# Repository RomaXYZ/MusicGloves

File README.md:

# EE445L_Final_Project
Codebase for EE445L final project, Spring 2022 (music gloves lol)

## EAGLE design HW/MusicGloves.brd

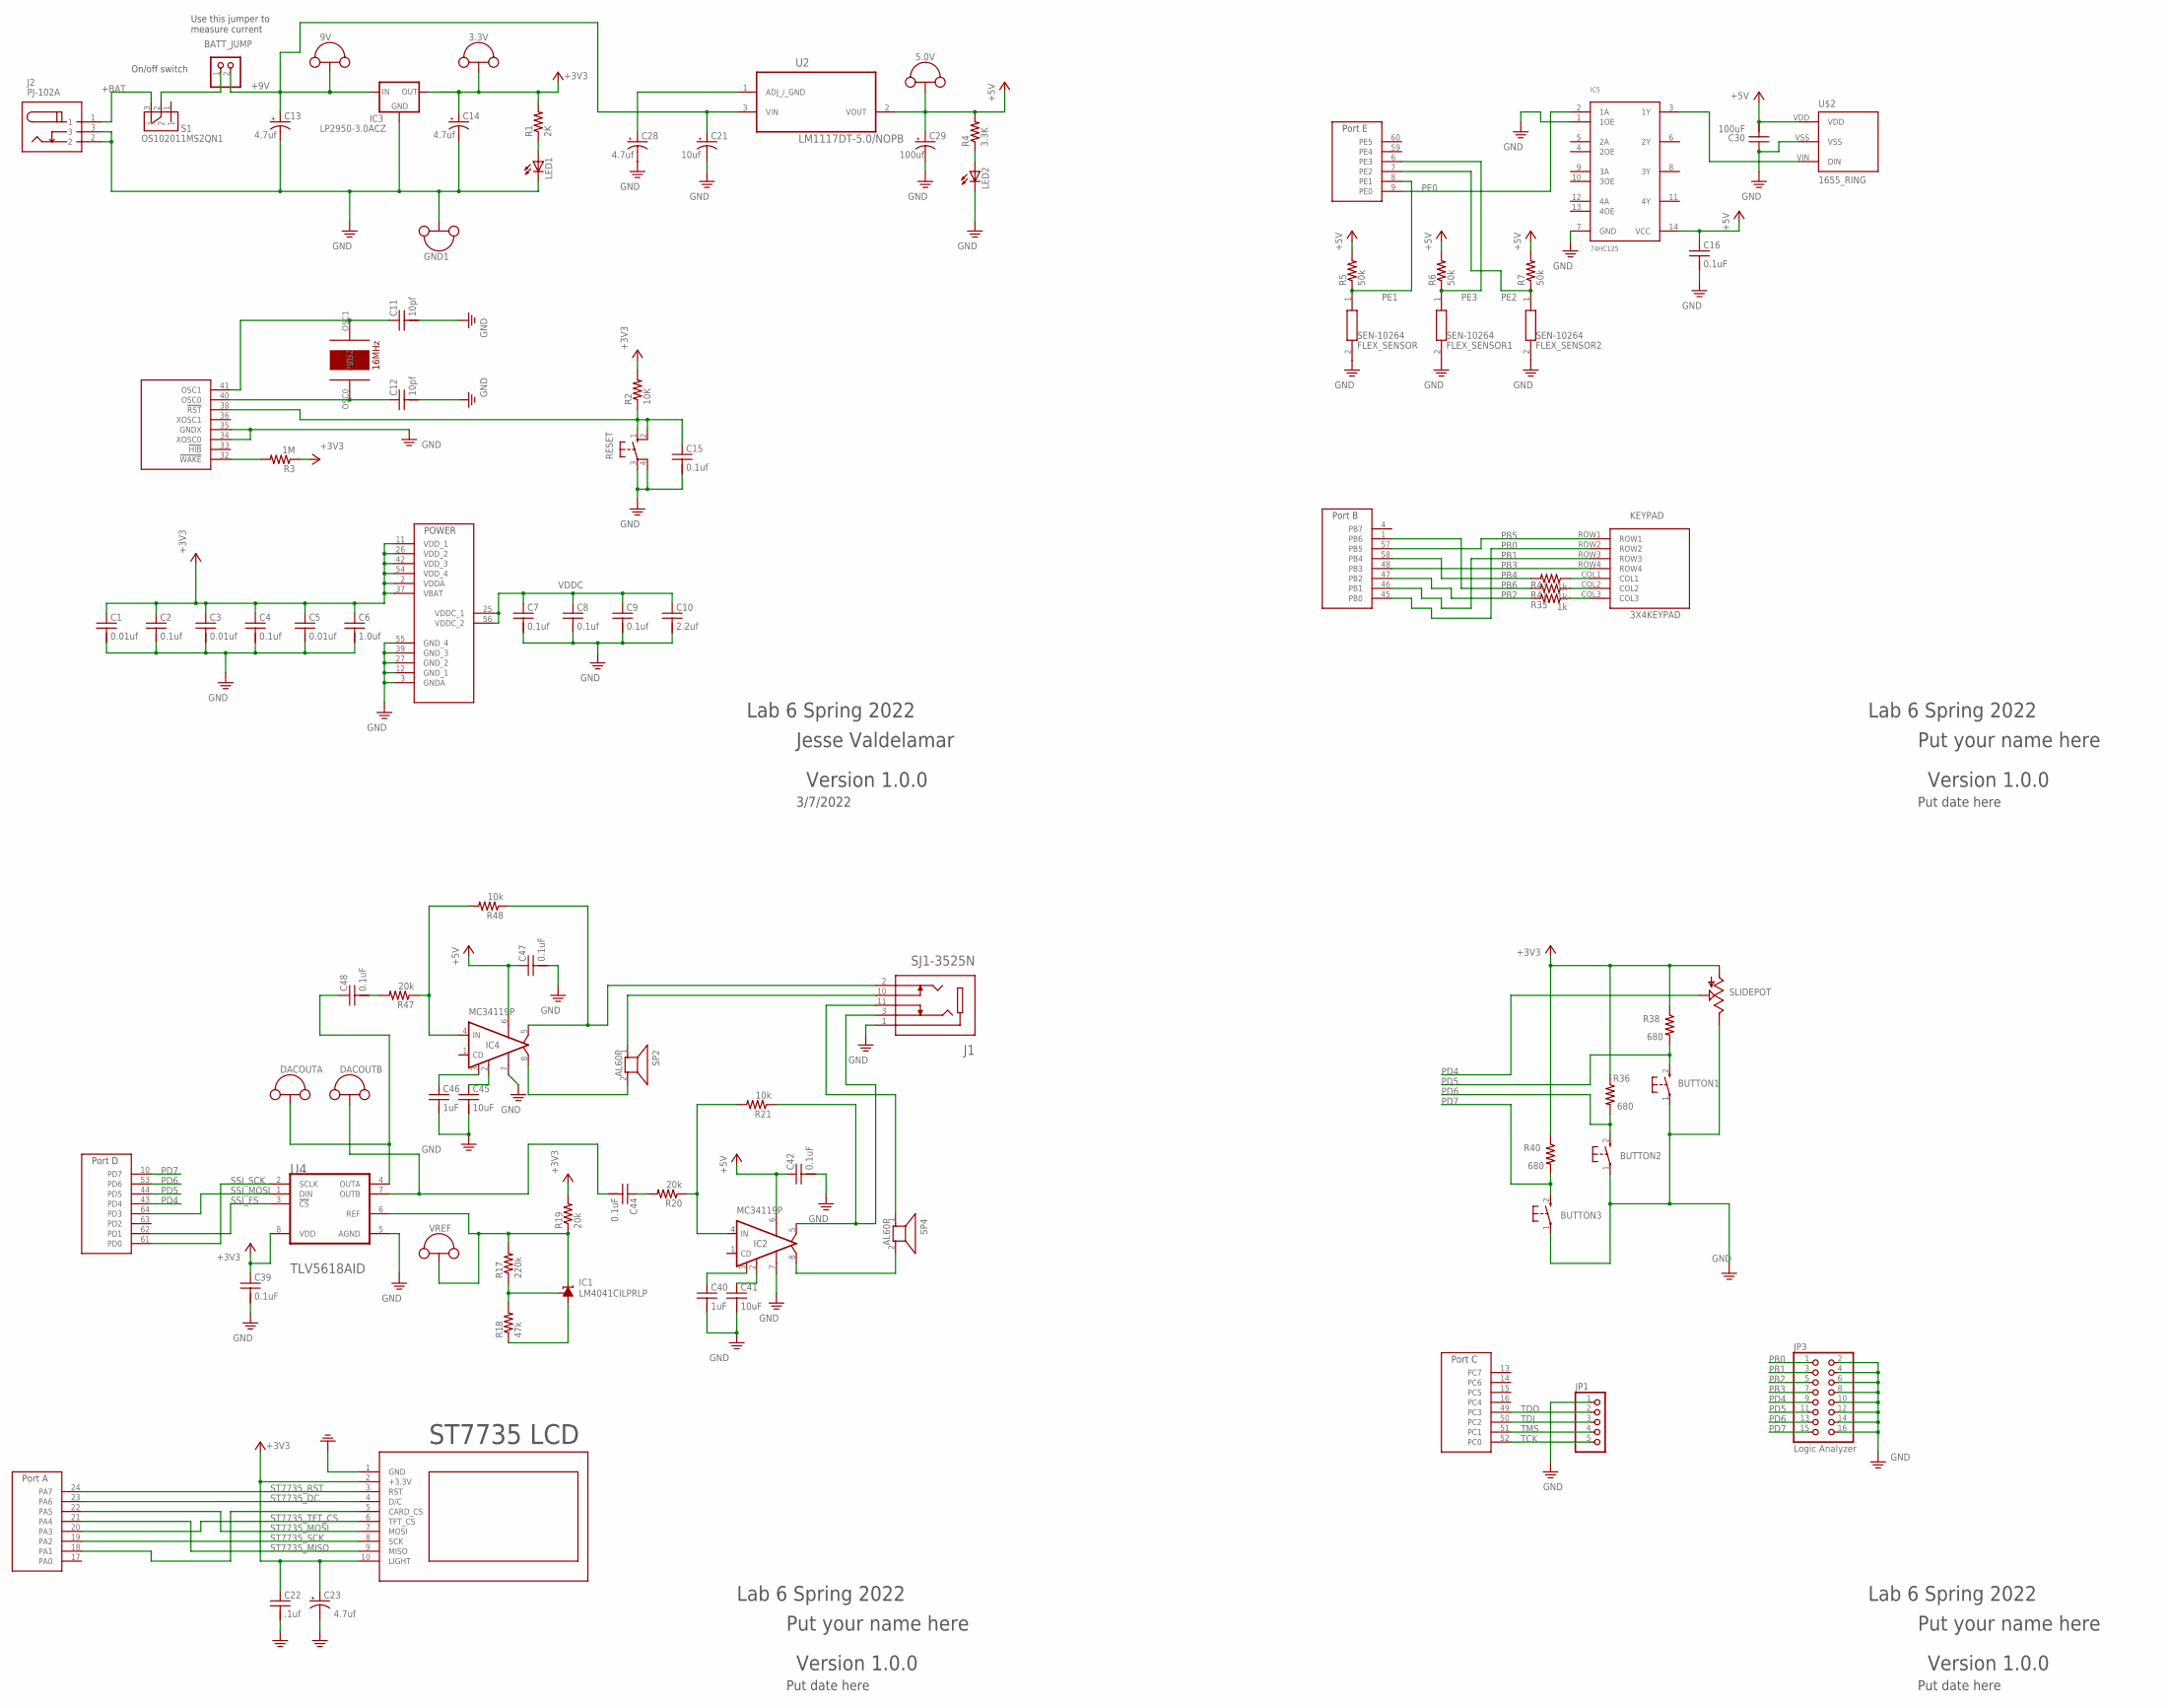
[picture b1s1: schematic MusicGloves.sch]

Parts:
3.3V, 5.0V, 9V: TP_LOOP
BATT_JUMP: PINHD-1X2; 1X02
BUTTON1, BUTTON2, BUTTON3: B3F_1052_2HOLE; B3F-10XX_2HOLE
C1, C3, C5: 0.01uf; CAP100MIL
C2, C4, C7, C8, C9, C15: 0.1uf; CAP100MIL
C6: 1.0uf; CAP100MIL
C10: 2.2uf; CAP100MIL
C11, C12: 10pf; CAP100MIL
C13, C14, C23, C28: 4.7uf; CAP200MILPOLARIZED
C16, C39, C42, C44, C47, C48: 0.1uF; CAP200MIL
C21: 10uf; CAP200MILPOLARIZED
C22: .1uf; CAP200MIL
C29: 100uf; CAP200MILPOLARIZED
C30: 100uF; CAP200MIL
C40, C46: 1uF; CAP200MIL
C41, C45: 10uF; CAP200MIL
DACOUTA: TP_LOOP
DACOUTB: TP_LOOP
FLEX_SENSOR, FLEX_SENSOR1, FLEX_SENSOR2: SEN-10264; RESAD2700W1900L700D500
GND1: TP_LOOP
IC1: LM4041CILPRLP; LP_O-PBCY-W3
IC2, IC4: MC34119P; DIL08
IC3: LP2950-3.0ACZ; TO92
IC5: 74HC125; SOIC-14
J1: SJ1-3525N; CUI_SJ1-3525N
J2: PJ-102A; PJ-102AH
JP1: PINHD-1X5; 1X05
JP3: Logic Analyzer; 2X08
KEYPAD: 3X4KEYPAD
LED1, LED2: LED3MM
R1: 2K; RES200MIL
R2: 10K; RES200MIL
R3: 1M; RES200MIL
R4: 3.3K; RES200MIL
R5, R6, R7: 50k; RES200MIL
R17: 220k; RES200MIL
R18: 47k; RES200MIL
R19, R20, R47: 20k; RES200MIL
R21, R48: 10k; RES200MIL
R35, R41, R43: 1k; 0204/5
R36, R38, R40: 680; 0204/5
RESET: B3F-1052; B3F-10XX
S1: OS102011MS2QN1; SW_OS102011MS2QN1
SLIDEPOT: POTENTIOMETER_PTA2043B25U; PTA2043
SP2, SP4: AL60P
U1: TM4C123GH6PM; QFP50P1200X1200X160-64N
U2: LM1117DT-5.0/NOPB; TO228P970X238-3N
U4: TEXAS_INSTRUMENTS_TLV5618AIDTEXAS_INSTRUMENTS_TLV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; TEXAS_INSTRUMENTS_TLV5618AID_0
U$2: 1655_RING; LED_1655_RING
U$3: ST7735
VREF: TP_LOOP
Y1: 16MHZ_CRYSTAL

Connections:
+3V1: IC1.2 (C), R17.2, R19.1, U4.6 (REF), VREF.P$1, VREF.P$2
+3V2: C48.1, DACOUTA.P$1, DACOUTA.P$2, U4.4 (OUTA)
+3V3: 3.3V.P$1, 3.3V.P$2, C1.1, C2.1, C3.1, C4.1, C5.1, C6.1, C14.+, C22.1, C23.+, C39.1, IC3.1 (OUT), R1.2, R2.2, R3.1, R19.2, R36.1, R38.1, R40.1, SLIDEPOT.3 (A), U1.2 (VDDA), U1.11 (VDD_1), U1.26 (VDD_2), U1.37 (VBAT), U1.42 (VDD_3), U1.54 (VDD_4), U4.8 (VDD), U$3.2 (+3.3V), U$3.10 (LIGHT)
+3V4: C44.2, DACOUTB.P$1, DACOUTB.P$2, U4.7 (OUTB)
+5V: 5.0V.P$1, 5.0V.P$2, C16.1, C29.+, C30.2, C42.1, C47.1, IC2.6 (VCC), IC4.6 (VCC), IC5.14 (VCC), R4.2, R5.2, R6.2, R7.2, U2.2 (VOUT), U$2.VDD
+9V: 9V.P$1, 9V.P$2, BATT_JUMP.2, C13.+, C21.+, IC3.3 (IN), U2.3 (VIN)
+BAT: J2.1, S1.3
COL1: KEYPAD.COL1, R43.1
COL2: KEYPAD.COL2, R41.1
COL3: KEYPAD.COL3, R35.1
GND: BUTTON1.1, BUTTON2.1, BUTTON3.1, C1.2, C2.2, C3.2, C4.2, C5.2, C6.2, C7.2, C8.2, C9.2, C10.2, C11.2, C12.2, C13.-, C14.-, C15.2, C16.2, C21.-, C22.2, C23.-, C28.-, C29.-, C30.1, C39.2, C40.2, C41.2, C42.2, C45.2, C46.2, C47.2, FLEX_SENSOR.2, FLEX_SENSOR1.2, FLEX_SENSOR2.2, GND1.P$1, GND1.P$2, IC2.7 (GND), IC3.2 (GND), IC4.7 (GND), IC5.1 (1OE), IC5.7 (GND), J1.1, J2.2, J2.3, JP1.1, JP3.2, JP3.4, JP3.6, JP3.8, JP3.10, JP3.12, JP3.14, JP3.16, LED1.K (C), LED2.K (C), RESET.3, RESET.4 (P1), SLIDEPOT.1 (E), U1.3 (GNDA), U1.12 (GND_1), U1.27 (GND_2), U1.34 (XOSC0), U1.35 (GNDX), U1.39 (GND_3), U1.55 (GND_4), U4.5 (AGND), U$2.VSS, U$3.1 (GND)
unnamed: J1.10, SP2.1
unnamed: J1.11, SP4.1
unnamed: C44.1, R20.2
unnamed: C28.+, U2.1 (ADJ_/_GND)
unnamed: IC2.4 (IN), R20.1, R21.2
unnamed: IC2.8 (VO2), SP4.2
unnamed: C41.1, IC2.2 (FC2)
unnamed: C40.1, IC2.3 (FC1)
unnamed: U1.18 (PA1), U$3.5 (CARD_CS)
unnamed: IC5.3 (1Y), U$2.VIN (DIN)
unnamed: C48.2, R47.2
unnamed: IC4.4 (IN), R47.1, R48.2
unnamed: IC4.8 (VO2), SP2.2
unnamed: C45.1, IC4.2 (FC2)
unnamed: C46.1, IC4.3 (FC1)
OSC0: C12.1, U1.40 (OSC0), Y1.OSC0
OSC1: C11.1, U1.41 (OSC1), Y1.OSC1
PB0: JP3.1, KEYPAD.ROW2, U1.45 (PB0)
PB1: JP3.3, KEYPAD.ROW3, U1.46 (PB1)
PB2: JP3.5, R35.2, U1.47 (PB2)
PB3: JP3.7, KEYPAD.ROW4, U1.48 (PB3)
PB4: R43.2, U1.58 (PB4)
PB5: KEYPAD.ROW1, U1.57 (PB5)
PB6: R41.2, U1.1 (PB6)
PD4: JP3.9, SLIDEPOT.2 (S), U1.43 (PD4)
PD5: BUTTON1.2 (S), JP3.11, R38.2, U1.44 (PD5)
PD6: BUTTON2.2 (S), JP3.13, R36.2, U1.53 (PD6)
PD7: BUTTON3.2 (S), JP3.15, R40.2, U1.10 (PD7)
PE0: IC5.2 (1A), U1.9 (PE0)
PE1: FLEX_SENSOR.1, R5.1, U1.8 (PE1)
PE2: FLEX_SENSOR2.1, R7.1, U1.7 (PE2)
PE3: FLEX_SENSOR1.1, R6.1, U1.6 (PE3)
POWERLED: LED1.A, R1.1
POWERLED1: LED2.A, R4.1
POWERLED3: IC4.5 (VO1), J1.2, R48.1
POWERLED14: IC1.1 (FB), R17.1, R18.2
POWERLED15: IC1.3 (A), R18.1
POWERLED17: IC2.5 (VO1), J1.3, R21.1
RESET: C15.1, R2.1, RESET.1 (S), RESET.2 (S1), U1.38 (!RST)
SSI_FS: U1.62 (PD1), U4.3 (!CS!)
SSI_MOSI: U1.64 (PD3), U4.1 (DIN)
SSI_SCK: U1.61 (PD0), U4.2 (SCLK)
ST7735_DC: U1.23 (PA6), U$3.4 (D/C)
ST7735_MISO: U1.21 (PA4), U$3.9 (MISO)
ST7735_MOSI: U1.22 (PA5), U$3.7 (MOSI)
ST7735_RST: U1.24 (PA7), U$3.3 (RST)
ST7735_SCK: U1.19 (PA2), U$3.8 (SCK)
ST7735_TFT_CS: U1.20 (PA3), U$3.6 (TFT_CS)
SWITCHEDPOWER: BATT_JUMP.1, S1.2
TCK: JP1.5, U1.52 (PC0)
TDI: JP1.3, U1.50 (PC2)
TDO: JP1.2, U1.49 (PC3)
TMS: JP1.4, U1.51 (PC1)
VDDC: C7.1, C8.1, C9.1, C10.1, U1.25 (VDDC_1), U1.56 (VDDC_2)
WAKE: R3.2, U1.32 (!WAKE)

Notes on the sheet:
Use this jumper to measure current
Lab 6 Spring 2022
Jesse Valdelamar
Version 1.0.0
3/7/2022
Put your name here
Put date here
On/off switch
ST7735 LCD

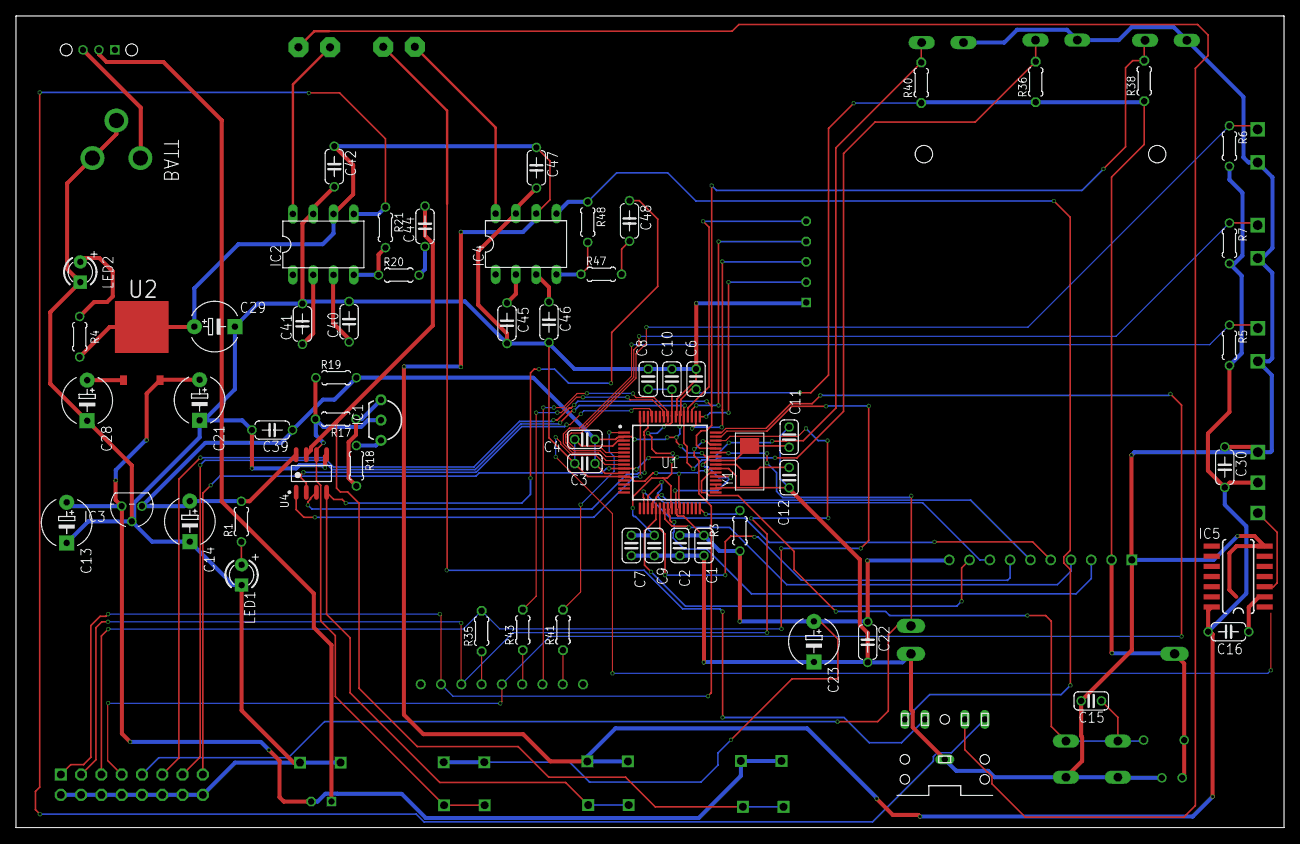
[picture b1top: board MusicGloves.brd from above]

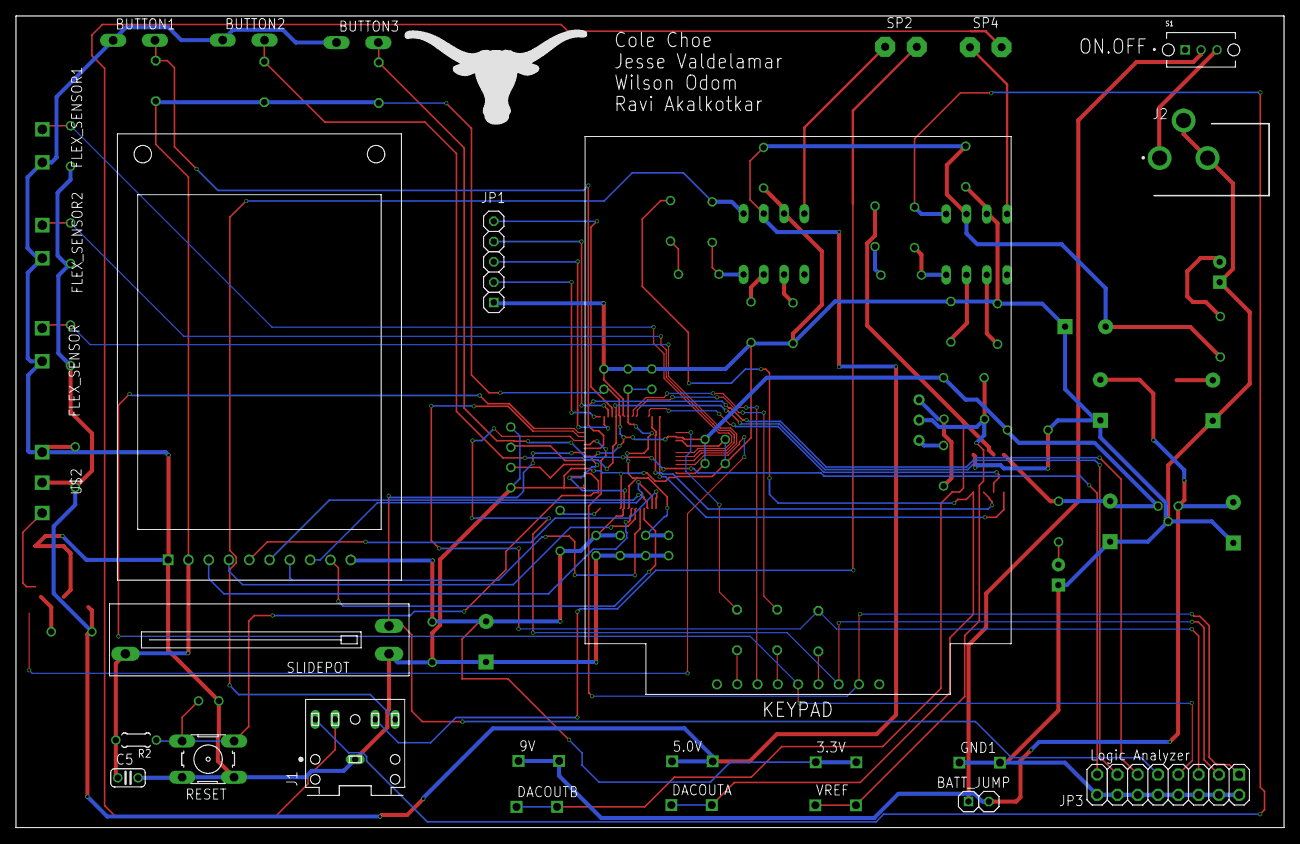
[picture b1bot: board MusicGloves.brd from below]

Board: 2 copper layers, 158.7 x 101.6 mm, 88 parts (26 on the bottom side), 66 nets.

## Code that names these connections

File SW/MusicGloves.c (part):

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 * @note Potential Pinouts:
 *    Backlight (pin 10) connected to +3.3 V
 *    MISO (pin 9) unconnected
 *    SCK (pin 8) connected to PA2 (SSI0Clk)
 *    MOSI (pin 7) connected to PA5 (SSI0Tx)
 *    TFT_CS (pin 6) connected to PA3 (SSI0Fss)
 *    CARD_CS (pin 5) unconnected
 *    Data/Command (pin 4) connected to PA6 (GPIO)
 *    RESET (pin 3) connected to PA7 (GPIO)
 *    VCC (pin 2) connected to +3.3 V
 *    Gnd (pin 1) connected to ground
 * 
 *    Center of 10k-ohm potentiometer connected to PE2/AIN1
 *    Bottom of 10k-ohm potentiometer connected to ground
 *    Top of 10k-ohm potentiometer connected to +3.3V 
 *
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int main_NeoPixel(void) { // Main for testing the neopixels
    DisableInterrupts();
    /* TExaS Debug modes:
       SCOPE,           // PD3
       LOGICANALYZER,   // ???
       SCOPE_PD2,       // PD2
       SCOPE_PE2,       // PE3
       SCOPE_PB5        // PB5
     */
		// Beginning on Initializations
		PLL_Init(Bus80MHz);              // now running at 80 MHz
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int main_lcddisplay(void) { // Main for testing LCD Display
    DisableInterrupts();
    /* TExaS Debug modes:
       SCOPE,           // PD3
       LOGICANALYZER,   // ???
       SCOPE_PD2,       // PD2
       SCOPE_PE2,       // PE3
       SCOPE_PB5        // PB5
     */
		// Beginning on Initializations
		PLL_Init(Bus80MHz);              // now running at 80 MHz
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
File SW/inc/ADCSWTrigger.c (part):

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  ADC0_ACTSS_R |= 0x0008;         // 14) enable sample sequencer 3
}

// PD0 is AIN7
void ADC0_InitSWTriggerSeq3_Ch7(void){ 
  SYSCTL_RCGCADC_R |= 0x0001;   // 7) activate ADC0 
                                  // 1) activate clock for Port D
  SYSCTL_RCGCGPIO_R |= 0x08;  // D
  while((SYSCTL_PRGPIO_R&0x08) != 0x08){};
  GPIO_PORTD_DIR_R &= ~0x01;      // 2) make PE4 input
  GPIO_PORTD_AFSEL_R |= 0x01;     // 3) enable alternate function on PD0
  GPIO_PORTD_DEN_R &= ~0x01;      // 4) disable digital I/O on PD0
  GPIO_PORTD_AMSEL_R |= 0x01;     // 5) enable analog functionality on PD0
    
  while((SYSCTL_PRADC_R&0x0001) != 0x0001){};    // good code, but not yet implemented in simulator

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  delay = SYSCTL_RCGCGPIO_R;
  delay = SYSCTL_RCGCGPIO_R;
  switch(channelNum){
    case 0:                       //      Ain0 is on PE3
      GPIO_PORTE_DIR_R &= ~0x08;  // 3.0) make PE3 input
      GPIO_PORTE_AFSEL_R |= 0x08; // 4.0) enable alternate function on PE3
      GPIO_PORTE_DEN_R &= ~0x08;  // 5.0) disable digital I/O on PE3
      GPIO_PORTE_AMSEL_R |= 0x08; // 6.0) enable analog functionality on PE3
      break;
    case 1:                       //      Ain1 is on PE2
      GPIO_PORTE_DIR_R &= ~0x04;  // 3.1) make PE2 input
      GPIO_PORTE_AFSEL_R |= 0x04; // 4.1) enable alternate function on PE2
      GPIO_PORTE_DEN_R &= ~0x04;  // 5.1) disable digital I/O on PE2
      GPIO_PORTE_AMSEL_R |= 0x04; // 6.1) enable analog functionality on PE2
      break;
    case 2:                       //      Ain2 is on PE1
      GPIO_PORTE_DIR_R &= ~0x02;  // 3.2) make PE1 input
      GPIO_PORTE_AFSEL_R |= 0x02; // 4.2) enable alternate function on PE1
      GPIO_PORTE_DEN_R &= ~0x02;  // 5.2) disable digital I/O on PE1
      GPIO_PORTE_AMSEL_R |= 0x02; // 6.2) enable analog functionality on PE1
      break;
    case 3:                       //      Ain3 is on PE0
      GPIO_PORTE_DIR_R &= ~0x01;  // 3.3) make PE0 input
      GPIO_PORTE_AFSEL_R |= 0x01; // 4.3) enable alternate function on PE0
      GPIO_PORTE_DEN_R &= ~0x01;  // 5.3) disable digital I/O on PE0
      GPIO_PORTE_AMSEL_R |= 0x01; // 6.3) enable analog functionality on PE0
      break;
    case 4:                       //      Ain4 is on PD3
      GPIO_PORTD_DIR_R &= ~0x08;  // 3.4) make PD3 input
      GPIO_PORTD_AFSEL_R |= 0x08; // 4.4) enable alternate function on PD3
      GPIO_PORTD_DEN_R &= ~0x08;  // 5.4) disable digital I/O on PD3
      GPIO_PORTD_AMSEL_R |= 0x08; // 6.4) enable analog functionality on PD3
      break;
    case 5:                       //      Ain5 is on PD2
      GPIO_PORTD_DIR_R &= ~0x04;  // 3.5) make PD2 input
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      GPIO_PORTD_DEN_R &= ~0x04;  // 5.5) disable digital I/O on PD2
      GPIO_PORTD_AMSEL_R |= 0x04; // 6.5) enable analog functionality on PD2
      break;
    case 6:                       //      Ain6 is on PD1
      GPIO_PORTD_DIR_R &= ~0x02;  // 3.6) make PD1 input
      GPIO_PORTD_AFSEL_R |= 0x02; // 4.6) enable alternate function on PD1
      GPIO_PORTD_DEN_R &= ~0x02;  // 5.6) disable digital I/O on PD1
      GPIO_PORTD_AMSEL_R |= 0x02; // 6.6) enable analog functionality on PD1
      break;
    case 7:                       //      Ain7 is on PD0
      GPIO_PORTD_DIR_R &= ~0x01;  // 3.7) make PD0 input
      GPIO_PORTD_AFSEL_R |= 0x01; // 4.7) enable alternate function on PD0
      GPIO_PORTD_DEN_R &= ~0x01;  // 5.7) disable digital I/O on PD0
      GPIO_PORTD_AMSEL_R |= 0x01; // 6.7) enable analog functionality on PD0
      break;
    case 8:                       //      Ain8 is on PE5
      GPIO_PORTE_DIR_R &= ~0x20;  // 3.8) make PE5 input
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      GPIO_PORTE_DEN_R &= ~0x10;  // 5.9) disable digital I/O on PE4
      GPIO_PORTE_AMSEL_R |= 0x10; // 6.9) enable analog functionality on PE4
      break;
    case 10:                      //       Ain10 is on PB4
      GPIO_PORTB_DIR_R &= ~0x10;  // 3.10) make PB4 input
      GPIO_PORTB_AFSEL_R |= 0x10; // 4.10) enable alternate function on PB4
      GPIO_PORTB_DEN_R &= ~0x10;  // 5.10) disable digital I/O on PB4
      GPIO_PORTB_AMSEL_R |= 0x10; // 6.10) enable analog functionality on PB4
      break;
    case 11:                      //       Ain11 is on PB5
      GPIO_PORTB_DIR_R &= ~0x20;  // 3.11) make PB5 input
      GPIO_PORTB_AFSEL_R |= 0x20; // 4.11) enable alternate function on PB5
      GPIO_PORTB_DEN_R &= ~0x20;  // 5.11) disable digital I/O on PB5
      GPIO_PORTB_AMSEL_R |= 0x20; // 6.11) enable analog functionality on PB5
      break;
  }
  SYSCTL_RCGCADC_R |= 0x00000001; // 7) activate ADC0 (actually doesn't work)
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// Sequencer 2 priority: 3rd
// Sequencer 3 priority: 4th (lowest)
// SS2 triggering event: software trigger, busy-wait sampling
// SS2 1st sample source: AIN6 (PD1)
// SS2 2nd sample source: AIN5 (PD2)
// SS2 3st sample source: AIN4 (PD3)
// SS2 interrupts: enabled after 3rd sample but not promoted to controller
// 'task' is a pointer to a user function called in SS2 interrupt
// the user function has three parameters that get the x-, y-, and
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  SYSCTL_RCGCGPIO_R |= 0x08;    // activate clock for Port D
                                // allow time for clock to stabilize
  while((SYSCTL_PRGPIO_R&0x08) == 0){};
  GPIO_PORTD_DIR_R &= ~0x0E;    // make PD3-1 input
  GPIO_PORTD_AFSEL_R |= 0x0E;   // enable alternate function on PD3-1
  GPIO_PORTD_DEN_R &= ~0x0E;    // disable digital I/O on PD3-1
  GPIO_PORTD_AMSEL_R |= 0x0E;   // enable analog functionality on PD3-1
  // **** ADC0 SS2 initialization ****
  SYSCTL_RCGCADC_R |= 0x01;     // activate clock for ADC0
                                // allow time for clock to stabilize
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  uint32_t x, y, z;
  ADC0_PSSI_R = 0x0004;         // 1) initiate SS2
  while((ADC0_RIS_R&0x04)==0){};// 2) wait for conversion done
  x = ADC0_SSFIFO2_R&0xFFF;     // 3A) read 12-bit result from AIN6 (PD1)
  y = ADC0_SSFIFO2_R&0xFFF;     // 3B) read 12-bit result from AIN5 (PD2)
  z = ADC0_SSFIFO2_R&0xFFF;     // 3C) read 12-bit result from AIN4 (PD3)
  UserTask2(x, y, z);           // 4)  call the user function
  ADC0_ISC_R = 0x0004;          // 5) acknowledge completion
}
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}


// Initializes ADC0(PE3), ADC1(PE2), ADC2(PE1) and ADC3(PE0) sampling
// 125k max sampling
// SS2 triggering event: software trigger, busy-wait sampling
// SS2 1st sample source: Ain0 (PE3)
// SS2 2nd sample source: Ain1 (PE2)
// SS2 3rd sample source: Ain2 (PE1)
// SS2 4th sample source: Ain3 (PE0)
// SS2 interrupts: enabled after 4th sample but not promoted to controller
void ADC_Init3210(void){ 
  volatile uint32_t delay;                         
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  SYSCTL_RCGCGPIO_R |= 0x10;      // 1) activate clock for Port E
  while((SYSCTL_PRGPIO_R&0x10) == 0){};
  while((SYSCTL_PRADC_R&0x0001) != 0x0001){};    // good code, but not yet implemented in simulator
  GPIO_PORTE_DIR_R &= ~0x0E;      // 3) make PE3-1 input
  GPIO_PORTE_AFSEL_R |= 0x0E;     // 4) enable alternate function on PE3-1
  GPIO_PORTE_DEN_R &= ~0x0E;      // 5) disable digital I/O on PE3-1
  GPIO_PORTE_PCTL_R = GPIO_PORTE_PCTL_R&0xFFFF000F;
  GPIO_PORTE_AMSEL_R |= 0x0E;     // 6) enable analog functionality on PE3-1
  ADC0_PC_R &= ~0xF;              // 8) clear max sample rate field
  ADC0_PC_R |= 0x1;               //    configure for 125K samples/sec
  ADC0_SSPRI_R = 0x3210;          // 9) Sequencer 3 is lowest priority
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// Busy-wait Analog to digital conversion
// Input: none
// Output: four 12-bit result of ADC conversions
// Samples ADC0(PE3), ADC1(PE2), ADC2(PE1) and ADC3(PE0) 
// 125k max sampling
// software trigger, busy-wait sampling
// data returned by reference
// data[0] is ADC3 (PE0) 0 to 4095
// data[1] is ADC2 (PE1) 0 to 4095
// data[2] is ADC1 (PE2) 0 to 4095
// data[3] is ADC0 (PE3) 0 to 4095
void ADC_In3210(uint32_t data[3]){ 
  ADC0_PSSI_R = 0x0004;            // 1) initiate SS2
  while((ADC0_RIS_R&0x04)==0){};   // 2) wait for conversion done
  //data[0] = ADC0_SSFIFO2_R&0xFFF;  // 3A) PE0 result
  data[0] = ADC0_SSFIFO2_R&0xFFF;  // 3A) PE1 result
  data[1] = ADC0_SSFIFO2_R&0xFFF;  // 3A) PE2 result
  data[2] = ADC0_SSFIFO2_R&0xFFF;  // 3B) PE3 result
  ADC0_ISC_R = 0x0004;             // 4) acknowledge completion
}

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
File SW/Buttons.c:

// filename ******** Buttons.c **************
// This files involves interfacing the buttons and the keypad
// Date: 3/30/2022
// Created by Wilson Odom
// Lab Number 17525
// TA Mohit
// Date of Last Revision: 4/8/2022

/** File includes. */
#include <stdio.h>
#include <stdint.h>
#include "./inc/tm4c123gh6pm.h"
#include "./inc/Timer2A.h"
#include "./inc/Timer3A.h"
#include "./inc/Timer4A.h"
#include "./inc/CortexM.h"

#define NVIC_EN0_INT2           0x00000004  // Interrupt 2 enable
#define NVIC_EN0_INT3           0x00000008  // Interrupt 3 enable

// SW1 corresponds to PC4
// SW2 corresponds to PC5
// SW3 corresponds to PC6
volatile uint8_t SW1, SW2, SW3;
uint16_t switch_debouncing;
uint8_t set = 0;

void switch_debouncer(void);

///****************Button_Init****************
// Initializes 3 Buttons on Ports PC4-PC6
// Remember to change this to match the diagram post-PCB
void Button_Init(void){
	
// Port C version, PC4-PC6
	SYSCTL_RCGCGPIO_R |= 0x04; // Activate clock for Port C
	SW1, SW2, SW3 = 0; // Clear all 3 semaphores
	
	GPIO_PORTC_DIR_R &= ~0x70; // Make PC4-PC6 in
	GPIO_PORTC_DEN_R |= 0x70; // Enable Digital I/o on PC4-PC6
	GPIO_PORTC_IS_R &= ~0x70; // PC4-PC6 is edge sensitive
	GPIO_PORTC_IBE_R &= ~0x70; // PC4-PC6, single edge
	GPIO_PORTC_IEV_R |= 0x70; // Rising edge
	GPIO_PORTC_ICR_R = 0x70; // Clear Flag 4, 5 and 6
	GPIO_PORTC_IM_R |= 0x70; // ARM interrupts
	
	NVIC_PRI0_R = (NVIC_PRI0_R& 0xFF00FFFF) | 0x00400000; // PortC = priority 2
	NVIC_EN0_R = (NVIC_EN0_INT2); // Enable Interrupt 2
	
	switch_debouncing = 0;
	set = 0;
	
	//EnableInterrupts();
	
// Port D Version, PD5-PD7
//	SYSCTL_RCGCGPIO_R |= 0x08; // Activate clock for Port D
//	SW1, SW2, SW3 = 0; // Clear all 3 semaphores
//	
//	GPIO_PORTD_DIR_R &= ~0xD0; // Make PD5-PD7 in
//	GPIO_PORTD_DEN_R |= 0xD0; // Enable Digital I/o on PD5-PD7
//	GPIO_PORTD_IS_R &= ~0xD0; // PD5-PD7 is edge sensitive
//	GPIO_PORTD_IBE_R &= ~0xD0; // PD5-PD7, single edge
//	GPIO_PORTD_IEV_R |= 0xD0; // Rising edge
//	GPIO_PORTD_ICR_R = 0xD0; // Clear Flags for PD5-PD7
//	GPIO_PORTD_IM_R |= 0xD0; // ARM interrupts
//	
//	NVIC_PRI0_R = (NVIC_PRI0_R& 0x0FFFFFFF) | 0x40000000; // PortD = priority 2
//	NVIC_EN0_R = (NVIC_EN0_INT3); // Enable Interrupt 3
//	EnableInterrupts();
		
	
	
}

void GPIOPortC_Handler(void){
	// Debounce, wait 20 ms to find the true value
	if(switch_debouncing == 0){
		
		// Get the value of the of the switches pressed
		if((GPIO_PORTC_RIS_R >> 4) & 0x01){
			SW1 = 1;
			switch_debouncing = 1;
		}else if((GPIO_PORTC_RIS_R >> 5) & 0x01){
			SW2 = 1;
			switch_debouncing = 2;
		}else if((GPIO_PORTC_RIS_R >> 6) & 0x01){
			SW3 = 1;
			switch_debouncing = 3;
		}
		set = 1;
		Timer4A_Init(&switch_debouncer, 1000000, 2);
	}
	GPIO_PORTC_ICR_R = 0x70; // Acknowledge all 3 flags
	
}

//void GPIOPortD_Handler(void){
//		// Debounce, wait 20 ms to find the true value
//	GPIO_PORTD_ICR_R = 0x70; // Acknowledge all 3 flags
//	if(switch_debouncing == 0){
//		SW1 = (GPIO_PORTC_RIS_R & 0x01);
//		SW2 = (GPIO_PORTC_RIS_R >> 1) & 0x01;
//		SW3 = (GPIO_PORTC_RIS_R >> 2) & 0x01;
//		Timer4A_Init(&switch_debouncer, 1600000, 2);
//		switch_debouncing = 1; // You are now debouncing!
//	}
//}

void wait_for_fall(void){
	if(!((GPIO_PORTC_DATA_R>>(3+switch_debouncing))&1)){
		Timer4A_Stop();
		Timer4A_Init(&switch_debouncer, 1000000, 2);
		set=0;
	}
}
void switch_debouncer(void){
		//switch_debouncing = 0; // You are no longer debouncing!
		Timer4A_Stop();
		if(set){
			Timer4A_Init(&wait_for_fall, 1000000, 2);
		}
		else{
			switch_debouncing=0;
		}
}



uint8_t GetSW1(void){
	uint8_t copy = SW1;
	SW1 = 0;
	return(copy);
}
uint8_t GetSW2(void){
	uint8_t copy = SW2;
	SW2 = 0;
	return(copy);
}
uint8_t GetSW3(void){
	uint8_t copy = SW3;
	SW3 = 0;
	return(copy);
}



///****************SlidePot_Init****************
// Initializes a single slide pot on Port PD2 to function as an ADC
// Initializes ADC1
void SlidePot_Init(void){
	volatile uint32_t delay;
	SYSCTL_RCGCADC_R |= 0x00000002; // 1) Activate ADC1
	SYSCTL_RCGCGPIO_R |= 0x08; // 1) Activate clock for Port D
	
	while((SYSCTL_PRGPIO_R  & 0x08) == 0){}; // Wait for Port D clock to stabilize
	while((SYSCTL_PRADC_R & 0x0002) != 0x0002){}; // Wait for ADC2 to stabilize
	
	GPIO_PORTD_DIR_R &= ~0x04; // 3) Make PD2 an input
	GPIO_PORTD_AFSEL_R &= 0x04; // 4) Enable alt function on PD2
	GPIO_PORTD_DEN_R &= ~0x04; // 5) Disable digital I/O on PD2
	GPIO_PORTD_PCTL_R &= 0xFFFFF0FF; // PD2
	GPIO_PORTD_AMSEL_R &= 0x04; // 6) Enable Analog Funct. on PD2
		
	ADC1_PC_R &= ~0xF; 							// 8 )Clear Max Sample Field on ADC1	
	ADC1_PC_R |= 0x1; 							// Configure for 125k samples / second
	ADC1_SSPRI_R = 0x3210;          // 9) Sequencer 3 is lowest priority
  ADC1_ACTSS_R &= ~0x0004;        // 10) disable sample sequencer 2
  ADC1_EMUX_R &= ~0x0F00;         // 11) seq2 is software trigger
  ADC1_SAC_R = 0x06;              // 32-point average
  //ADC1_SSMUX2_R = 0x0123;         // 12) set channels for SS2
	ADC1_SSMUX2_R = 0x0005;         // 12) set channels for SS2, Channel 5	
  ADC1_SSCTL2_R = 0x0006;         // 13) no TS0 D0 IE0 END0 TS1 D1, yes IE1 END1
  ADC1_IM_R &= ~0x0004;           // 14) disable SS2 interrupts
  ADC1_ACTSS_R |= 0x0004;         // 15) enable sample sequencer 2	
			
		
}

int slidePot_Get(void){
	ADC1_PSSI_R = 0x0004; // 1) Initiate SS2
	int data;
	while((ADC1_RIS_R & 0x04) == 0){}; // 2) Wait for conversion to be done
	data = ADC1_SSFIFO2_R & 0xFFF;
	ADC1_ISC_R = 0x0004;
		
	return(data);
}

int GetVolume(void){
	int slidepot = slidePot_Get();
	
	// Map this to 0 - 100
	int temp = (slidepot / 40);
	if(temp < 2){
		return(0);
	}
	else if (temp > 100){
		return(100);
	}
	else{
		return(temp - 1);
	}
}

void KeypadScan1(void);
void KeypadScan2(void);
void keypadDebouncer(void);


int RowData = 0x20;
int prevRowData = 0x08;
int RowNum = 0;
int ColNum = 0;
int pressed = 0;
int scanning = 0;
uint8_t set2 = 0;
///****************Keypad_Init***************
// Initializes a keypad on Ports PB0-PB6
void Keypad_Init(void){
	volatile unsigned long delay;

  SYSCTL_RCGCGPIO_R |= 0x00000002;  // 1) activate clock for Port B
  delay = SYSCTL_RCGCGPIO_R;        // allow time for clock to start
                                    // 2) no need to unlock GPIO Port C
  GPIO_PORTB_AMSEL_R = 0;      			// 3) disable analog on PB0-6
  GPIO_PORTB_PCTL_R = 0; 						// 4) PCTL GPIO on PC0-6
  GPIO_PORTB_DIR_R = 0x2B;       	 	// 5) direction PB2,4,6 input, PB0,1,3,5 output
  GPIO_PORTB_AFSEL_R &= ~0x7F;      // 6) PB0-6 regular port function
  GPIO_PORTB_DEN_R |= 0x7F;         // 7) enable PB0-6 digital port
	GPIO_PORTB_IS_R &= ~0x54;							// Edge-triggered interrupt
	GPIO_PORTB_IBE_R &= ~0x54;				// Not both edges
	GPIO_PORTB_IEV_R |= 0x54;					// Rising Edge Triggered
	GPIO_PORTB_ICR_R = 0x54;					// clear flags 2, 4, 6
	GPIO_PORTB_IM_R |= 0x54;					// interrupt synchronization
	
	NVIC_PRI0_R = (NVIC_PRI0_R & 0xFFFF00FF) | 0x00004000; //priority 5
	NVIC_EN0_R = 2; //enable interrupt 1 in NVIC
	Timer2A_Init(KeypadScan2,80000,6);
	GPIO_PORTB_ICR_R = 0x54;					// clear flags 2, 4, 6
}
int x;
void GPIOPortB_Handler(void){
	x = GPIO_PORTB_RIS_R;
	if(!pressed&&!scanning&&!set2){
		pressed = 1;
		Timer2A_Stop();	
		Timer3A_Init(keypadDebouncer, 1600000, 6);
		if((GPIO_PORTB_RIS_R & 0x04) != 0){
			ColNum = 3;
		}
		else if((GPIO_PORTB_RIS_R & 0x10) != 0){
			ColNum = 1;
		} 
		else if((GPIO_PORTB_RIS_R & 0x40) != 0){
			ColNum = 2;
		}
		set2 = 1;
		
	}
	else
		x = 0;
	GPIO_PORTB_ICR_R  = 0x54;

}

void KeypadScan1(void) {
	int temp = GPIO_PORTB_DATA_R;
	if((GPIO_PORTB_DATA_R & ~0x2B) == 0){
		Timer2A_Stop();
		Timer3A_Init(keypadDebouncer, 1600000, 6);
		pressed = 1;
		set2 = 0;
	}
}


void KeypadScan2(void) {
	scanning = 1;
	if(!set2){
		GPIO_PORTB_DATA_R &= ~prevRowData;
		prevRowData = RowData;
		if(RowData == 0x20){
			RowData = 0x01;
			RowNum = 1;
		}
		else if(RowData == 0x01){
			RowData = 0x02;
			RowNum = 2;
		}
		else if(RowData == 0x02){
			RowData = 0x08;
			RowNum = 3;
		}
		else{
			RowData = 0x20;
			RowNum = 4;
		}
		GPIO_PORTB_DATA_R |= prevRowData;
	}
	scanning = 0;
}

void keypadDebouncer(void){
	pressed = 0;
	Timer3A_Stop();
	if(set2)
		Timer2A_Init(KeypadScan1,40000,6);
	else
		Timer2A_Init(KeypadScan2,80000,6);
}

///****************Buttons_Get***************
// Reads the values of all 5 buttons
int Buttons_Get(void){
	return -1;
}

///****************Keypad_Get***************
// Reads the values of the KeyPad
int Keypad_Get(void){
	if(ColNum == 0) return -1;
	int ret = -1;
	if(RowNum == 1){
		if(ColNum == 1) ret = 1;
		if(ColNum == 2) ret = 2;
		if(ColNum == 3) ret = 3;
	}	
	if(RowNum == 2){
		if(ColNum == 1) ret = 4;
		if(ColNum == 2) ret = 5;
		if(ColNum == 3) ret = 6;
	}
	if(RowNum == 3){
		if(ColNum == 1) ret = 7;
		if(ColNum == 2) ret = 8;
		if(ColNum == 3) ret = 9;
	}
	if(RowNum == 4){
		if(ColNum == 1) ret = 10;
		if(ColNum == 2) ret = 0;
		if(ColNum == 3) ret = 11;
	}
	ColNum = 0;
	return ret;
}

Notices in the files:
SW/MusicGloves.c:
@copyright Copyright (c) 2022
"Embedded Systems: Real Time Interfacing to Arm Cortex M Microcontrollers",
ISBN: 978-1463590154, Jonathan Valvano, copyright (c) 2021
Copyright 2022 by Jonathan W. Valvano, valvano@mail.utexas.edu
SW/inc/ADCSWTrigger.c:
ISBN: 978-1463590154, Jonathan Valvano, copyright (c) 2020
Copyright 2020 by Jonathan W. Valvano, valvano@mail.utexas.edu
